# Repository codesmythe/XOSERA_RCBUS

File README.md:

[Xosera](https://github.com/XarkLabs/Xosera) is an FPGA based "retro"
graphics adapter created by @Xark.  Check out the link to see all of
its features (which are summarized in the image below). Xosera was
originally designed for the rosco_m68k single board computer and the
bus interface for that board. But, Xosera features a simple 8-bit data
bus with a few control signals.  So, this project is a "port" of
Xosera to the [RCBus](https://smallcomputercentral.com/rcbus/) bus
interface. 

## Table of Contents
* [Hardware Documentation](#hardware-documentation)
  * [Schematic](#schematic)
  * [Connectors](#connectors)
  * [Jumpers](#jumpers)
  * [Bill of Materials](#bill-of-materials)
* [Programming the FPGA](#progamming-the-fpga)
* [Acknowledgements](#acknowledgements)

## Hardware Documentation

### Schematic

This four layer board was created using [Kicad](https://www.kicad.org) version 8.0.

Click the image below to download a PDF version of the schematic.

### Connectors

| Reference | Comment                      |
| --------- | ---------------------------- |
| J3        | 40-pin RCBus connector       |
| J5        | Female VGA monitor connector |
| J11       | Audio Jack                   |

### Jumpers

| Reference |                                                          | Description                   | Comment                                                      |
| --------- | -------------------------------------------------------- | ----------------------------- | ------------------------------------------------------------ |
| J4        |     | I/O Address decode            | The J4 jumper block controls where in the Z80 I/O space the XOSERA_RCBUS board will appear. The Xosera interface requires 32 bytes of I/O addresses, and can be configured to appear at I/O addresses 0x00-0x1F, 0x20-0x3F, 0x40-0x5F, 0x60-0x7F, 0x80-0x9F, 0xA0-0xBF, 0xC0-0xDF or 0xE0-0xFF |
| J6        |     | Interrupt connection to RCBus | The board can generate a single interrupt Xosera. Jumper the left two pins of J6 to use the /INT RCBus signal (pin 22) or the right two pins to use the RCBus USER1/INT1 signal (pin 37). |
| J8        |    | Upduino clock                 | This jumper must be closed for proper operation.             |
| J9        |    | Xosera debug pin              | Leave this jumper open under normal operation.               |
| J10       |  | IEI/IEO signals.              | Add two horizontal jumpers. These jumpers connect the XOSERA_RCBUS board to the RCBus system IEI/IEO  signals. Normally required. |

The default I/O address setting for this board is 0xA0.

## Bill of Materials (BOM)

[Text file parts list](XOSERA_RCBUS_mouser.txt) for pasting into the [Mouser BOM tool](https://www.mouser.com/Bom/CopyPaste) (login required).

Check out the [interactive BOM](https://htmlpreview.github.io/?https://raw.githubusercontent.com/codesmythe/XOSERA_RCBUS/refs/heads/main/XOSERA_RCBUS_V1A_ibom.html)
for the board.

To obtain a KEMOJO PCB, download these [Gerbers](https://raw.githubusercontent.com/codesmythe/XOSERA_RCBUS/refs/heads/main/XOSERA_RCBUS_V1A.zip) for use at your preferred PCB manufacturer. I use JLCPCB.

| Component Type     | Reference                  | Qty | Description                                                                                                                  | Part                                                                                     |
| ------------------ | -------------------------- | --- | ---------------------------------------------------------------------------------------------------------------------------- | ---------------------------------------------------------------------------------------- |
| FPGA Dev Board | (Plugs into J1 & J2) | 1 | Upduino 3.1 low cost Lattice iCE40 FPGA board | Purchase from [TinyVision.ai](https://tinyvision.ai/products/fpga-development-board-upduino-v3-1) or [Tindie](https://www.tindie.com/products/tinyvision_ai/upduino-v31-low-cost-lattice-ice40-fpga-board/?pt=ac_prod_search) |
| Capacitor          | C0                         |   1 | 47uF, Electrolytic, 2.5mm Pitch                                                                                              | Mouser [710-860020673013](https://www.mouser.com/ProductDetail/710-860020673013)         |
| Capacitor          | C1-C9 |   9 | 0.1 uF, MLCC, 5 mm Pitch                                                                                                     | Mouser [594-K104K15X7RF5TH5](https://www.mouser.com/ProductDetail/594-K104K15X7RF5TH5)   |
| Capacitor          | C10,C11                    |   2 | 4700pF, MLCC, 5 mm Pitch                                                                                                     | Mouser [594-K472K10X7RF5UH5](https://www.mouser.com/ProductDetail/594-K472K10X7RF5UH5)   |
| Diode              | D1                         |   1 | 1N5817                                                                                                                       | Mouser [511-1N5817](https://www.mouser.com/ProductDetail/511-1N5817)                     |
| Socket             | J1,J2                      |   2 | 1x24 female pin socket                                                                                                       | Mouser [517-929850-01-26-RA](https://www.mouser.com/ProductDetail/517-929850-01-26-RA)   |
| Connector          | J3                         |   1 | 1x40 right angle pin header                                                                                                  | Mouser [710-61304011021](https://www.mouser.com/ProductDetail/710-61304011021)           |
| Jumper Block       | J4                         |   1 | 2x8 straight pin header                                                                                                      | Mouser [200-TSW10807TD](https://www.mouser.com/ProductDetail/200-TSW10807TD)             |
| Connector          | J5                         |   1 | Female VGA connector | Mouser [523-7HDE15SD1CH4FVGA](https://www.mouser.com/ProductDetail/523-7HDE15SD1CH4FVGA) |
| Jumper Block       | J6                         |   1 | 2x2 right angle pin header                                                                                                   | Mouser [710-61300421021](https://www.mouser.com/ProductDetail/710-61300421021)           |
| Jumper             | J8,J9                      |   2 | 1x2 straight pin header                                                                                                      | Mouser [571-5-146268-1](https://www.mouser.com/ProductDetail/571-5-146268-1)             |
| Jumper Block       | J10                        |   1 | 2x2 straight pin header                                                                                                      | Mouser [737-PH2-04-UA](https://www.mouser.com/ProductDetail/737-PH2-04-UA)               |
| Connector          | J11                        |   1 | 3-pin Audio Jack, no switches                                                                                                | Mouser [SJ1-3533NG](https://www.mouser.com/ProductDetail/SJ1-3533NG)                     |
| Transistor         | Q1                         |   1 | 2N7000  MOSFET in TO92                                         | Mouser [512-2N7000](https://www.mouser.com/ProductDetail/512-2N7000)                     |
| Resistor           | R1,R2,R3                   |   3 | 470 ohm, axial, 1% tolerance, 1/4 W                                                                                          | Mouser [603-MFR-25FTF52-470R](https://www.mouser.com/ProductDetail/603-MFR-25FTF52-470R) |
| Resistor           | R4,R5,R6                   |   3 | 1K ohm, axial, 1% tolerance, 1/4 W                                                                                           | Mouser [603-MFR-25FTF52-1K](https://www.mouser.com/ProductDetail/603-MFR-25FTF52-1K)     |
| Resistor           | R7,R8,R9                   |   3 | 2.2K ohm, axial, 1% tolerance, 1/4 W                                                                                         | Mouser [603-MFR-25FTF52-2K2](https://www.mouser.com/ProductDetail/603-MFR-25FTF52-2K2)   |
| Resistor           | R10,R11                    |   2 | 47 ohm, axial, 1% tolerance, 1/4 W                                                                                           | Mouser [603-MFR-25FTF52-47R](https://www.mouser.com/ProductDetail/603-MFR-25FTF52-47R)   |
| Resistor           | R12,R13,R14,R17            |  4 | 4.7K ohm, axial, 1% tolerance, 1/4 W                                                                                         | Mouser [603-MFR-25FTF52-4K7](https://www.mouser.com/ProductDetail/603-MFR-25FTF52-4K7)   |
| Resistor           | R15,R16                    |   2 | 3.3K ohm, axial, 1% tolerance, 1/4 W                                                                                         | Mouser [603-MFR-25FRF52-3K3](https://www.mouser.com/ProductDetail/603-MFR-25FRF52-3K3)   |
| Integrated Circuit | U1                         |   1 | 74LS08 quad 2-input AND in 14-pin DIP                                                                                        | Mouser [595-SN74LS08N](https://www.mouser.com/ProductDetail/595-SN74LS08N)               |
| Integrated Circuit | U2,U3                      |   2 | 74LVC245 octal bus transceiver in 20-pin DIP                                                                                 | Mouser [595-SN74LVC245ANE4](https://www.mouser.com/ProductDetail/595-SN74LVC245ANE4)     |
| Integrated Circuit | U4                         |   1 | 74LS02 quad 2-pin NOR in 14-pin DIP                                                                                          | Mouser [595-SN74LS02N](https://www.mouser.com/ProductDetail/595-SN74LS02N)               |
| Integrated Circuit | U5                         |   1 | 74LS74 dual D flip flops in 14-pin DIP                                                                                       | Mouser [595-SN74LS74ANE4](https://www.mouser.com/ProductDetail/595-SN74LS74ANE4)         |
| Integrated Circuit | U6                         |   1 | 74LS138 3 to 8 decoder in 16-pin DIP                                                                                         | Mouser [595-SN74LS138N](https://www.mouser.com/ProductDetail/595-SN74LS138N)             |
| Integrated Circuit | U7                         |   1 | 74LS32 quad 2-pin OR in 14-pin DIP                                                                                           | Mouser [595-SN74LS32N](https://www.mouser.com/ProductDetail/595-SN74LS32N)               |
| Socket             | Sockets for U1,U4,U5,U7    |   4 | 14-pin DIP socket                                                                                                            | Mouser [571-1-2199298-3](https://www.mouser.com/ProductDetail/571-1-2199298-3)           |
| Socket             | Sockets for U2,U3           |   2 | 20-pin DIP socket                                                                                                            | Mouser [571-1-2199298-6](https://www.mouser.com/ProductDetail/571-1-2199298-6)           |
| Socket             | Socket for U6              |   1 | 16-pin DIP socket                                                                                                            | Mouser [571-1-2199298-4](https://www.mouser.com/ProductDetail/571-1-2199298-4)           |

## Programming the FPGA

The FPGA development board used by the Xosera graphics adapter is the [Upduino 3.1](https://tinyvision.ai/products/fpga-development-board-upduino-v3-1), which hosts a Lattice ICE40UP5K FPGA.

First, you will need the binary for the tool that actually does the programming, which is `iceprog.` This is available from the OSS CAD Suite tools. Download the Suite for your platform (Mac, Linux or Windows) from [here](https://github.com/YosysHQ/oss-cad-suite-build/releases).

Next, you will need the Xosera bitstream to load into the FPGA on the Upduino board. The bitstream is available 
[here](https://github.com/XarkLabs/Xosera/blob/develop/xosera_gateware/xosera_board_vga.bin). (Click on the "Download raw file" button third from right.). This file should be saved as `xosera_board_vga.bin`. 

For Windows, you will need the correct USB drivers. Installing those drivers is beyond the scope of this document, but relevant information can be found [here](https://github.com/FPGAwars/libftdi-cross-builder/wiki#driver-installation).

Then for any of the three platforms, at a command line prompt, use the `iceprog` (or `iceprog.exe`) program from the ISS Cad Suite to send the bitstream to the FPGA:

    $ iceprog -d i:0x0403:0x6014 xosera_board_vga.bin

*to be expanded*

## Acknowledgements

@Xark for creating the excellent Xosera project.

@roscopeco for designing the rosco_m68k Xosera [host board](https://github.com/rosco-m68k/hardware-projects/tree/master/xosera), from which I cribbed some of this design.

@lfantoniosi for his [tn_vdp](https://github.com/lfantoniosi/tn_vdp) project, from which I also borrowed a few ideas.

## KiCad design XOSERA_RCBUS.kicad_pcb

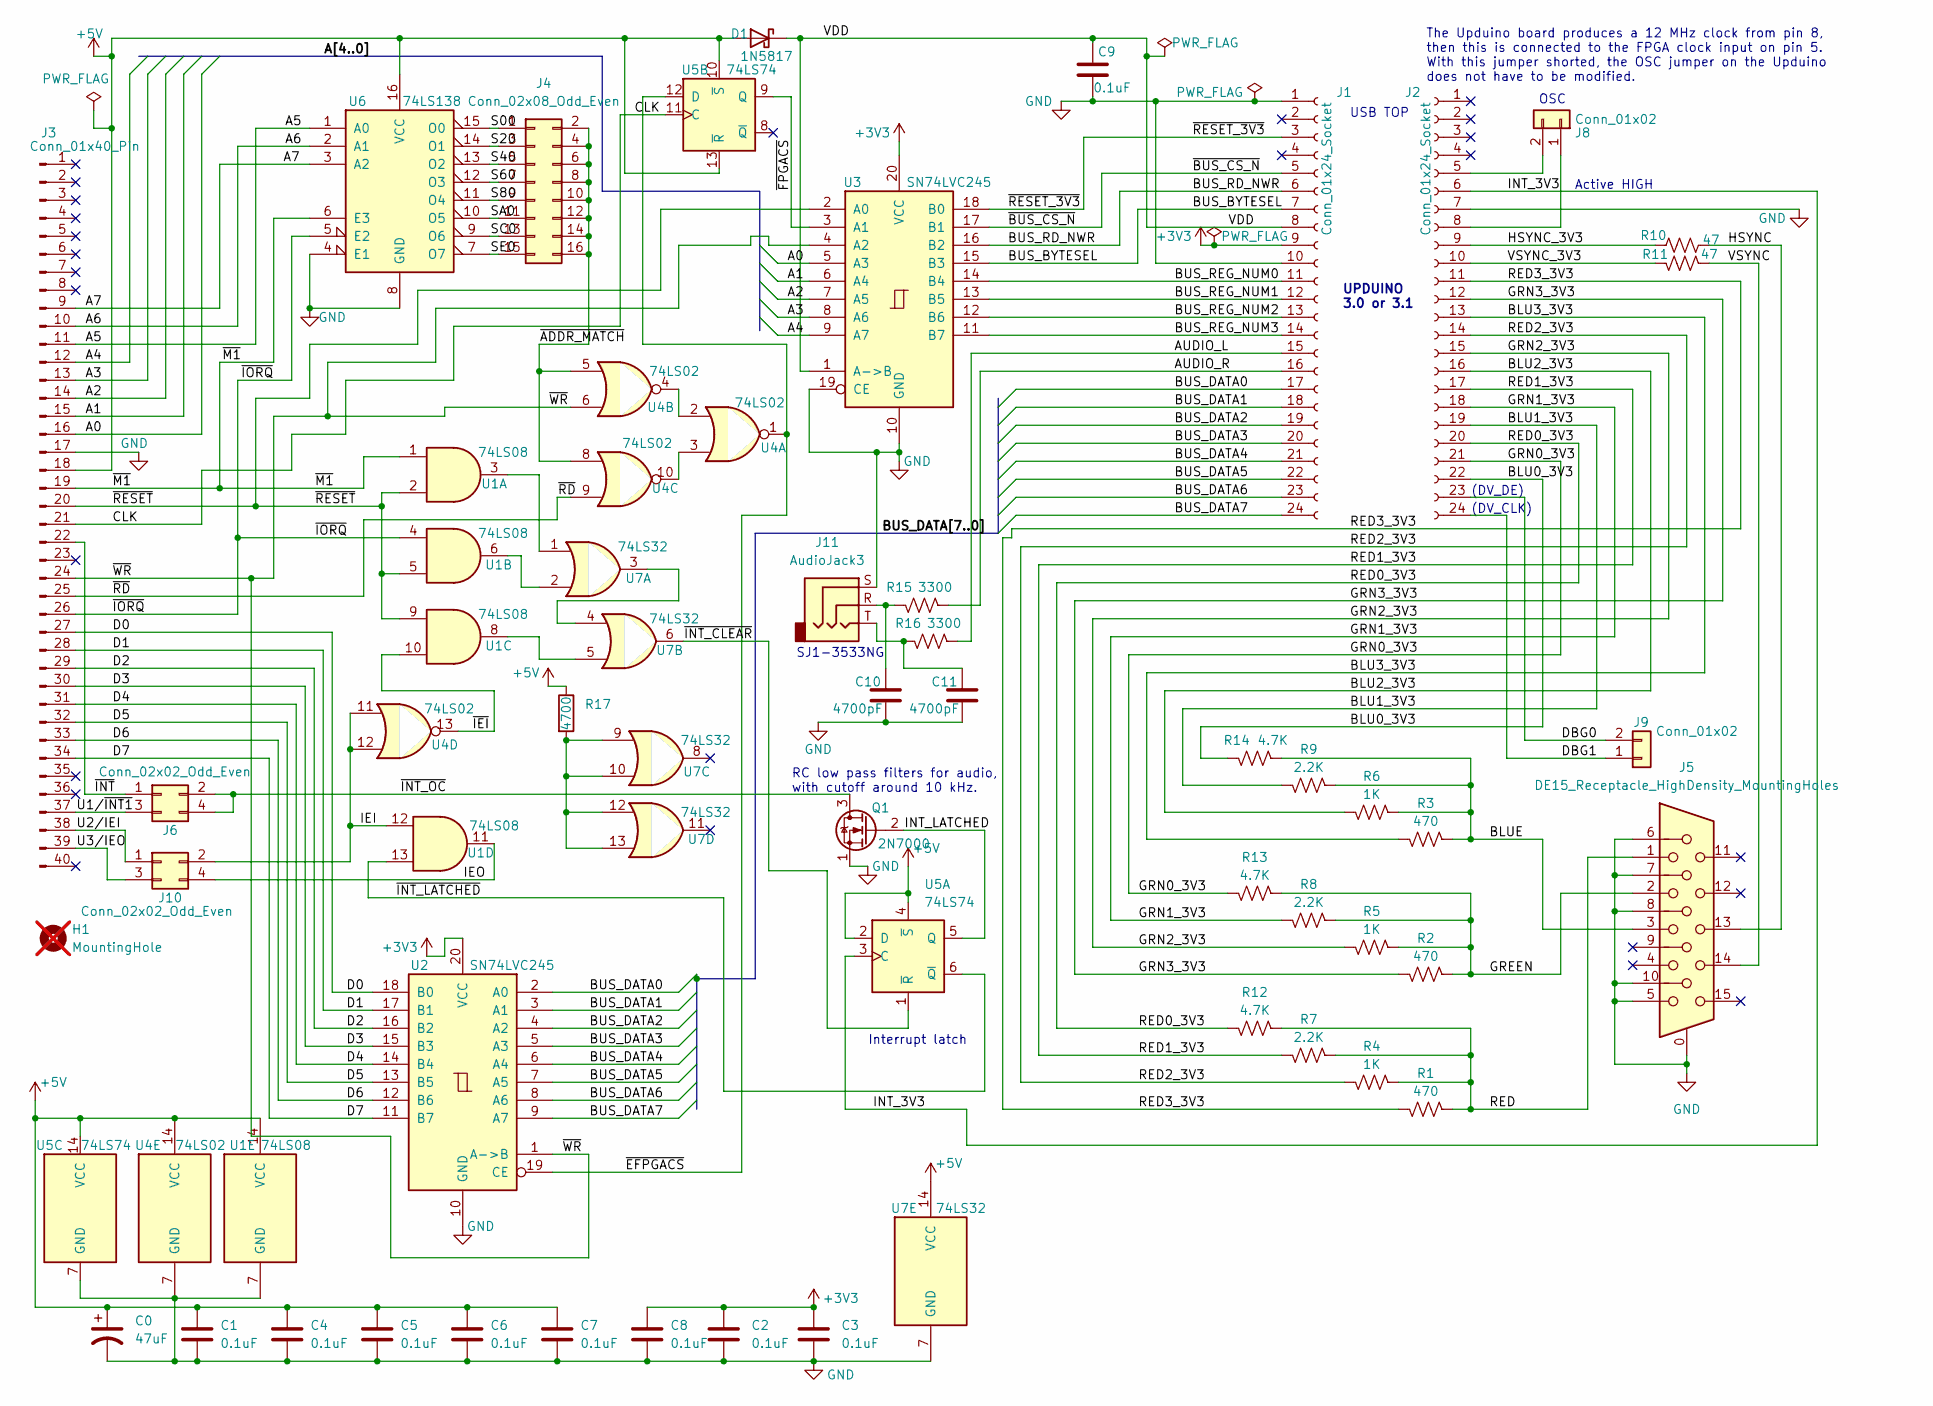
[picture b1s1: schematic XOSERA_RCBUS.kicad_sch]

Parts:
C0: 47uF; CP_Radial_D6.3mm_P2.50mm; PartNum00 710-860020673013
C1, C2, C3, C4, C5, C6, C7, C8, C9: 0.1uF; C_Rect_L7.0mm_W2.0mm_P5.00mm; PartNum00 594-K104K15X7RF5TH5
C10, C11: 4700pF; C_Rect_L7.0mm_W2.0mm_P5.00mm; PartNum00 594-K472K10X7RF5UH5
D1: 1N5817; D_DO-41_SOD81_P10.16mm_Horizontal; PartNum00 511-1N5817
H1: MountingHole; MountingHole_3.2mm_M3_ISO7380; not fitted
J1, J2: Conn_01x24_Socket; PinSocket_1x24_P2.54mm_Vertical; PartNum00 517-929850-01-26-RA
J3: Conn_01x40_Pin; PinHeader_1x40_P2.54mm_Vertical; PartNum00 710-61304011021
J4: Conn_02x08_Odd_Even; PinHeader_2x08_P2.54mm_Vertical; PartNum00 200-TSW10807TD
J5: DE15_Receptacle_HighDensity_MountingHoles; DSUB-15-Female_Right_Angle_VGA; PartNum00 523-7HDE15SD1CH4FVGA
J6: Conn_02x02_Odd_Even; PinHeader_2x02_P2.54mm_Horizontal; PartNum00 710-61300421021
J8, J9: Conn_01x02; PinHeader_1x02_P2.54mm_Vertical; PartNum00 571-5-146268-1
J10: Conn_02x02_Odd_Even; PinHeader_2x02_P2.54mm_Vertical; PartNum00 737-PH2-04-UA
J11: AudioJack3; Jack_3.5mm_CUI_SJ1-3533NG_Horizontal; PartNum00 SJ1-3533NG
Q1: 2N7000; TO-92_HandSolder; PartNum00 512-2N7000
R1, R2, R3: 470; R_Axial_DIN0207_L6.3mm_D2.5mm_P10.16mm_Horizontal; PartNum00 603-MFR-25FTF52-470R
R4, R5, R6: 1K; R_Axial_DIN0207_L6.3mm_D2.5mm_P10.16mm_Horizontal; PartNum00 603-MFR-25FTF52-1K
R7, R8, R9: 2.2K; R_Axial_DIN0207_L6.3mm_D2.5mm_P10.16mm_Horizontal; PartNum00 603-MFR-25FTF52-2K2
R10, R11: 47; R_Axial_DIN0207_L6.3mm_D2.5mm_P10.16mm_Horizontal; PartNum00 603-MFR-25FTF52-47R
R12, R13, R14: 4.7K; R_Axial_DIN0207_L6.3mm_D2.5mm_P10.16mm_Horizontal; PartNum00 603-MFR-25FTF52-4K7
R15, R16: 3300; R_Axial_DIN0207_L6.3mm_D2.5mm_P10.16mm_Horizontal; PartNum00 603-MFR-25FRF52-3K3
R17: 4700; R_Axial_DIN0207_L6.3mm_D2.5mm_P10.16mm_Horizontal; PartNum00 603-MFR-25FTF52-4K7
U1: 74LS08; DIP-14_W7.62mm_Socket_LongPads; PartNum00 595-SN74LS08N
U2, U3: SN74LVC245; DIP-20_W7.62mm_Socket_LongPads; PartNum00 595-SN74LVC245ANE4
U4: 74LS02; DIP-14_W7.62mm_Socket_LongPads; PartNum00 595-SN74LS02N
U5: 74LS74; DIP-14_W7.62mm_Socket_LongPads; PartNum00 595-SN74LS74ANE4
U6: 74LS138; DIP-16_W7.62mm_Socket_LongPads; PartNum00 595-SN74LS138N
U7: 74LS32; DIP-14_W7.62mm_Socket_LongPads; PartNum00 595-SN74LS32N

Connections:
+3V3: C2.1, C3.1, C8.1, J1.9, U2.20 (VCC), U3.20 (VCC)
+5V: C0.1, C1.1, C4.1, C5.1, C6.1, C7.1, D1.2 (A), J3.18, R17.1, U1.14 (VCC), U4.14 (VCC), U5.2 (D), U5.4 (~S), U5.10 (~S), U5.13 (~R), U5.14 (VCC), U6.16 (VCC), U7.14 (VCC)
/A0: J3.16, U3.5 (A3)
/A1: J3.15, U3.6 (A4)
/A2: J3.14, U3.7 (A5)
/A3: J3.13, U3.8 (A6)
/A4: J3.12, U3.9 (A7)
/A5: J3.11, U6.1 (A0)
/A6: J3.10, U6.2 (A1)
/A7: J3.9, U6.3 (A2)
/AUDIO_L: J1.15, R16.1
/AUDIO_R: J1.16, R15.1
/BLU0_3V3: J2.22, R14.2
/BLU1_3V3: J2.19, R9.2
/BLU2_3V3: J2.16, R6.2
/BLU3_3V3: J2.13, R3.2
/BLUE: J5.3, R3.1, R6.1, R9.1, R14.1
/BUS_BYTESEL: J1.7, U3.15 (B3)
/BUS_DATA0: J1.17, U2.2 (A0)
/BUS_DATA1: J1.18, U2.3 (A1)
/BUS_DATA2: J1.19, U2.4 (A2)
/BUS_DATA3: J1.20, U2.5 (A3)
/BUS_DATA4: J1.21, U2.6 (A4)
/BUS_DATA5: J1.22, U2.7 (A5)
/BUS_DATA6: J1.23, U2.8 (A6)
/BUS_DATA7: J1.24, U2.9 (A7)
/BUS_RD_NWR: J1.6, U3.16 (B2)
/BUS_REG_NUM0: J1.11, U3.14 (B4)
/BUS_REG_NUM1: J1.12, U3.13 (B5)
/BUS_REG_NUM2: J1.13, U3.12 (B6)
/BUS_REG_NUM3: J1.14, U3.11 (B7)
/CLK: J3.21, U5.11 (C)
/D0: J3.27, U2.18 (B0)
/D1: J3.28, U2.17 (B1)
/D2: J3.29, U2.16 (B2)
/D3: J3.30, U2.15 (B3)
/D4: J3.31, U2.14 (B4)
/D5: J3.32, U2.13 (B5)
/D6: J3.33, U2.12 (B6)
/D7: J3.34, U2.11 (B7)
/DBG0: J2.23, J9.2
/DBG1: J2.24, J9.1
/GREEN: J5.2, R2.1, R5.1, R8.1, R13.1
/GRN0_3V3: J2.21, R13.2
/GRN1_3V3: J2.18, R8.2
/GRN2_3V3: J2.15, R5.2
/GRN3_3V3: J2.12, R2.2
/HSYNC: J5.13, R10.2
/HSYNC_3V3: J2.9, R10.1
/IEI: J10.2, U1.12, U4.11, U4.12
/IEO: J10.4, U1.11
/INT_3V3: J2.6, U5.3 (C)
/INT_LATCHED: Q1.2 (G), U5.5 (Q)
/RED: J5.1, R1.1, R4.1, R7.1, R12.1
/RED0_3V3: J2.20, R12.2
/RED1_3V3: J2.17, R7.2
/RED2_3V3: J2.14, R4.2
/RED3_3V3: J2.11, R1.2
/S00: J4.1, U6.15 (O0)
/S20: J4.3, U6.14 (O1)
/S40: J4.5, U6.13 (O2)
/S60: J4.7, U6.12 (O3)
/S80: J4.9, U6.11 (O4)
/SA0: J4.11, U6.10 (O5)
/SC0: J4.13, U6.9 (O6)
/SE0: J4.15, U6.7 (O7)
/U1/~INT1: J3.37, J6.3
/U2/IEI: J3.38, J10.1
/U3/IEO: J3.39, J10.3
/VDD: C9.1, D1.1 (K), J1.8, U3.1 (A->B)
/VSYNC: J5.14, R11.1
/VSYNC_3V3: J2.10, R11.2
/~ADDR_MATCH: J4.2, J4.4, J4.6, J4.8, J4.10, J4.12, J4.14, J4.16, U4.5, U4.8
/~BUS_CS_N: J1.5, U3.17 (B1)
/~EFPGACS: U2.19 (CE), U4.1, U5.12 (D)
/~FPGACS: U3.3 (A1), U5.9 (Q)
/~IEI: U1.10, U4.13
/~INT_CLEAR: U5.1 (~R), U7.6
/~INT_LATCHED: U1.13, U5.6 (~Q)
/~INT_OC: J6.2, J6.4, Q1.3 (D)
/~INT: J3.22, J6.1
/~IORQ: J3.26, U1.4, U6.5 (E2)
/~M1: J3.19, U1.1, U6.6 (E3)
/~RD: J3.25, U4.9
/~RESET_3V3: J1.3, U3.18 (B0)
/~RESET: J3.20, U1.2, U1.5, U1.9, U3.2 (A0)
/~WR: J3.24, U2.1 (A->B), U3.4 (A2), U4.6
GND: C0.2, C1.2, C2.2, C3.2, C4.2, C5.2, C6.2, C7.2, C8.2, C9.2, C10.2, C11.2, J1.1, J1.10, J2.7, J3.17, J5.0, J5.5, J5.6, J5.7, J5.8, J5.10, J11.S, Q1.1 (S), U1.7 (GND), U2.10 (GND), U3.10 (GND), U3.19 (CE), U4.7 (GND), U5.7 (GND), U6.4 (E1), U6.8 (GND), U7.7 (GND)
unnamed: C10.1, J11.R, R15.2
unnamed: C11.1, J11.T, R16.2
unnamed: J2.5, J8.2
unnamed: J2.8, J8.1
unnamed: R17.2, U7.9, U7.10, U7.12, U7.13
unnamed: U1.3, U7.1
unnamed: U1.6, U7.2
unnamed: U1.8, U7.5
unnamed: U4.2, U4.4
unnamed: U4.3, U4.10
unnamed: U7.3, U7.4

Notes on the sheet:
USB TOP
(DV_DE)
Interrupt latch
(DV_CLK)
RC low pass filters for audio, with cutoff around 10 kHz.
UPDUINO 3.0 or 3.1
Active HIGH
OSC
SJ1-3533NG
The Upduino board produces a 12 MHz clock from pin 8, then this is connected to the FPGA clock input on pin 5. With this jumper shorted, the OSC jumper on the Upduino does not have to be modified.

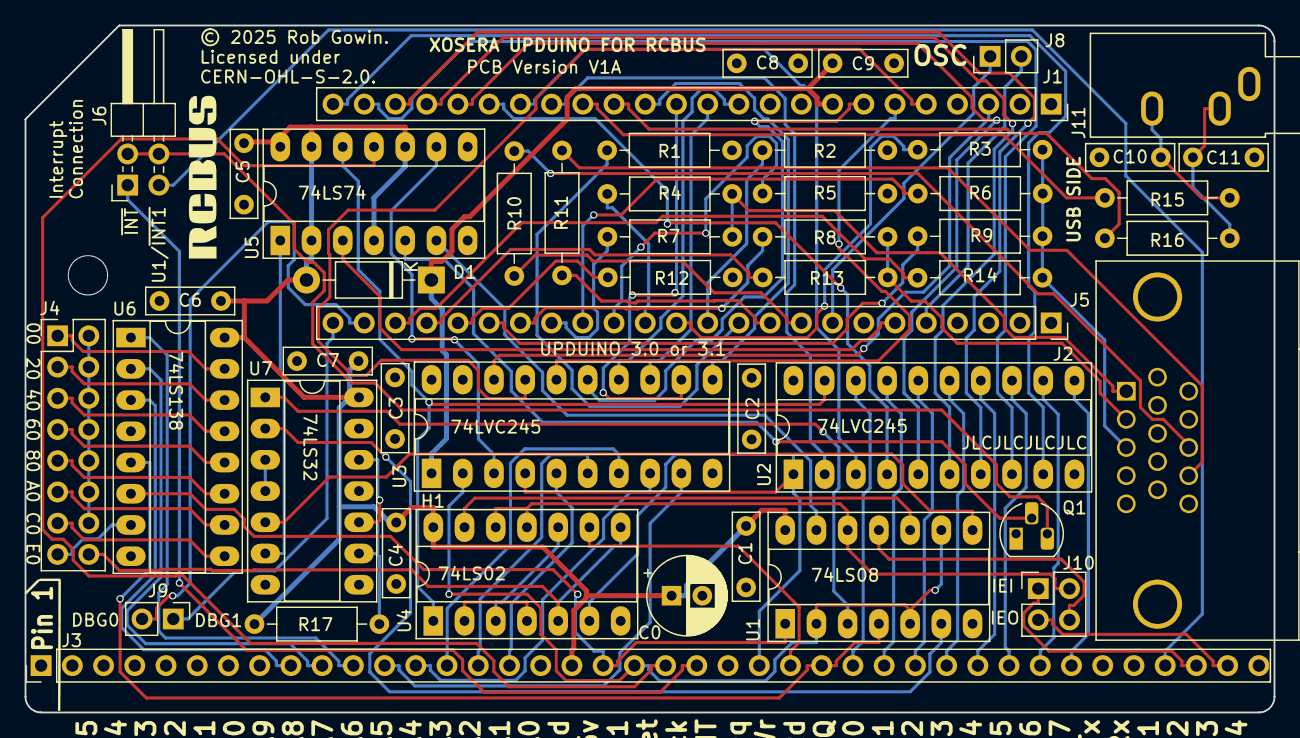
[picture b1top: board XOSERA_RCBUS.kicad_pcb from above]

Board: 4 copper layers, 101.6 x 55.9 mm, 49 parts (0 on the bottom side), 99 nets.

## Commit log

2025-06-16 Initial commit.
2025-06-16 Fix link in README.md
2025-06-20 Add Xosera slide.

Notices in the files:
XOSERA_RCBUS.kicad_pcb:
© 2025 Rob Gowin.
Licensed under
CERN-OHL-S-2.0.
XOSERA_RCBUS.kicad_sch:
© 2025 Rob Gowin. Licensed under CERN-OHL-S-2.0.
